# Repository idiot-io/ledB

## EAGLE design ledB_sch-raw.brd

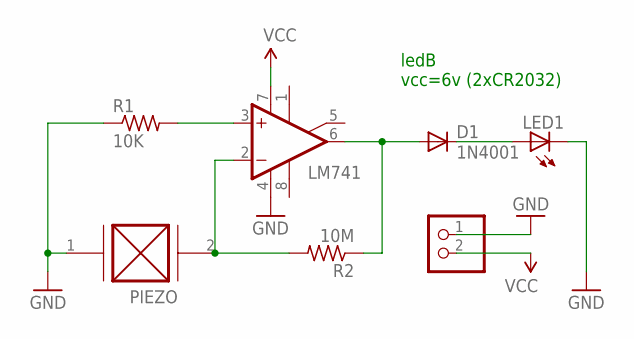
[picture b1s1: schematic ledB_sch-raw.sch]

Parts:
D1: 1N4001; DO-214AC
JP1: 6V+; 1X02_ROUND
LED1: LED1206; LED-1206
OPAMP: LM741; SO08
PIEZO: PIEZO; 1X02_ROUND
R1: 10K; M1206
R2: 10M; M1206

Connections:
GND: JP1.1, LED1.C, OPAMP.4 (V-), PIEZO.1 (GND), R1.1
unnamed: OPAMP.3 (+IN), R1.2
unnamed: D1.A, OPAMP.6 (OUT), R2.1
unnamed: D1.C, LED1.A
SIG: OPAMP.2 (-IN), PIEZO.2 (OUT+), R2.2
VCC: JP1.2, OPAMP.7 (V+)

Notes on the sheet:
ledB vcc=6v (2xCR2032)

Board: 2 copper layers, 7 parts (0 on the bottom side), 6 nets, no tracks yet.

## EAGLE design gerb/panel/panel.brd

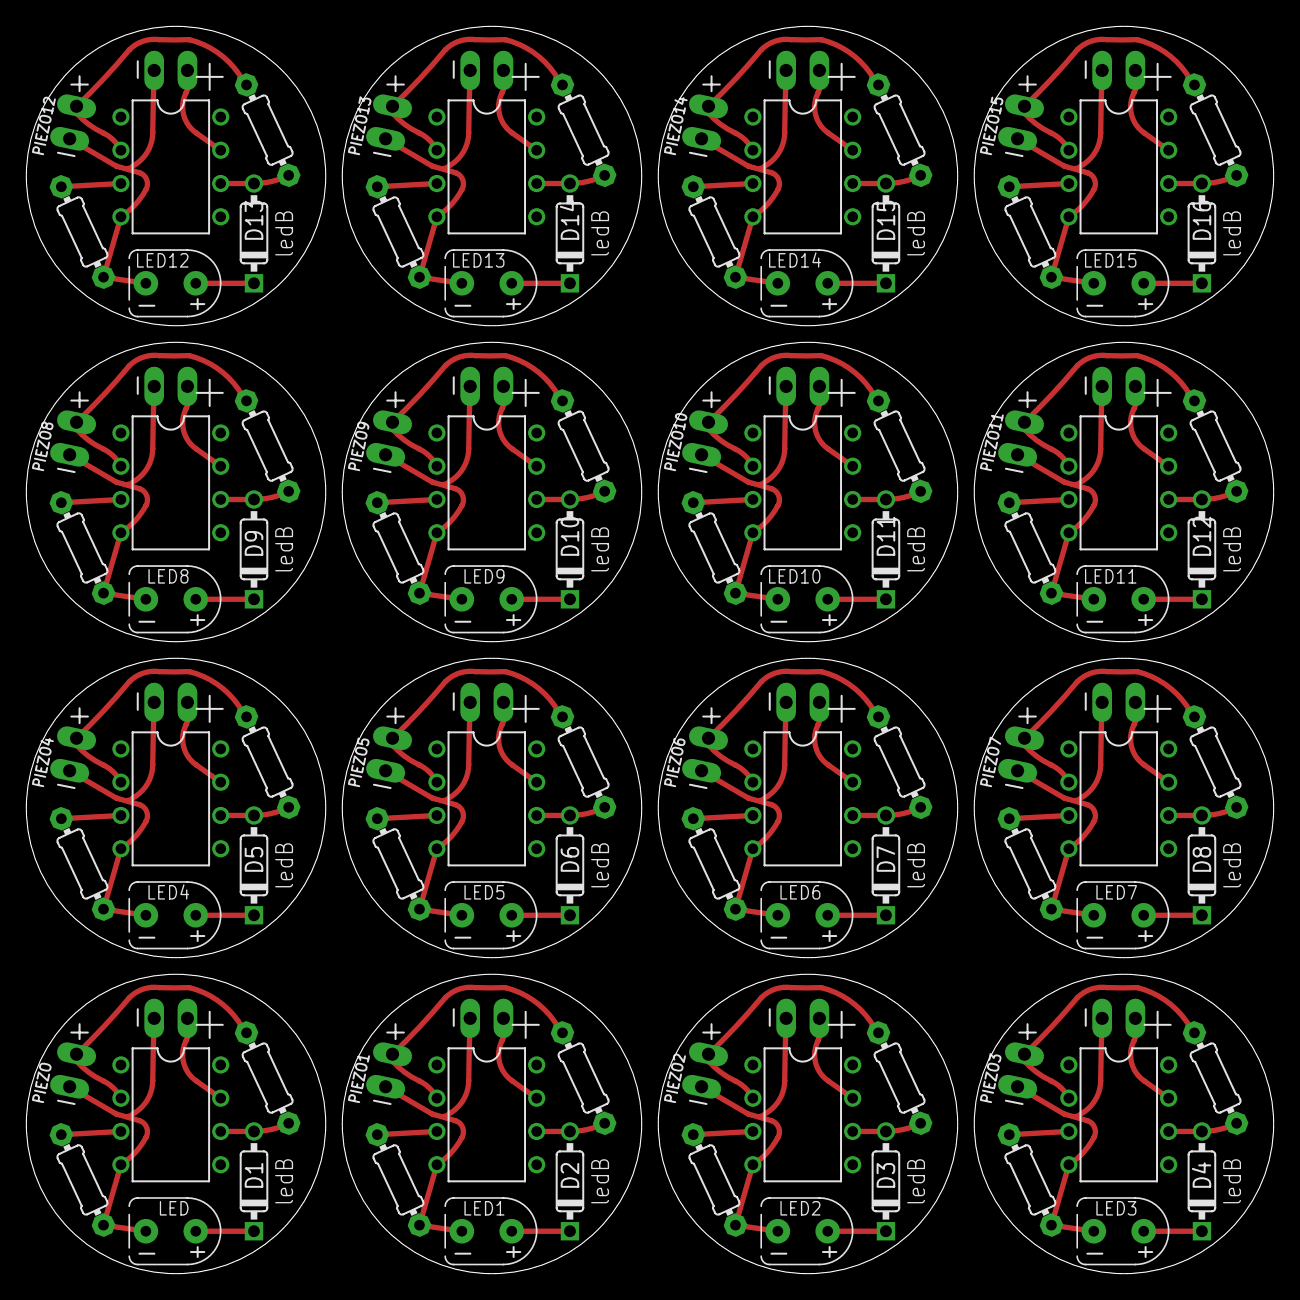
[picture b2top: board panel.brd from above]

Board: 2 copper layers, 95.2 x 95.2 mm, 112 parts (0 on the bottom side), 96 nets.

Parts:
D1, D2, D3, D4, D5, D6, D7, D8, D9, D10, D11, D12, D13, D14, D15, D16: diode; DO35-3
JP1, JP2, JP3, JP4, JP5, JP6, JP7, JP8, JP9, JP10, JP11, JP12, JP13, JP14, JP15, JP16: 6V+; 1X02_OVAL
LED, LED1, LED2, LED3, LED4, LED5, LED6, LED7, LED8, LED9, LED10, LED11, LED12, LED13, LED14, LED15: LED5MM
OPAMP, OPAMP1, OPAMP2, OPAMP3, OPAMP4, OPAMP5, OPAMP6, OPAMP7, OPAMP8, OPAMP9, OPAMP10, OPAMP11, OPAMP12, OPAMP13, OPAMP14, OPAMP15: LM741; DIL08
PIEZO, PIEZO1, PIEZO2, PIEZO3, PIEZO4, PIEZO5, PIEZO6, PIEZO7, PIEZO8, PIEZO9, PIEZO10, PIEZO11, PIEZO12, PIEZO13, PIEZO14, PIEZO15: PIEZO; 1X02_PEIZO
R1, R3, R5, R7, R9, R11, R13, R15, R17, R19, R21, R23, R25, R27, R29, R31: 10K; 0204/7
R2, R4, R6, R8, R10, R12, R14, R16, R18, R20, R22, R24, R26, R28, R30, R32: 10M; 0204/7

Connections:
GND: JP1.1, LED.K, OPAMP.4, PIEZO.1, R1.1
GND1: JP2.1, LED1.K, OPAMP1.4, PIEZO1.1, R3.1
GND2: JP3.1, LED2.K, OPAMP2.4, PIEZO2.1, R5.1
GND3: JP4.1, LED3.K, OPAMP3.4, PIEZO3.1, R7.1
GND4: JP5.1, LED4.K, OPAMP4.4, PIEZO4.1, R9.1
GND5: JP6.1, LED5.K, OPAMP5.4, PIEZO5.1, R11.1
GND6: JP7.1, LED6.K, OPAMP6.4, PIEZO6.1, R13.1
GND7: JP8.1, LED7.K, OPAMP7.4, PIEZO7.1, R15.1
GND8: JP9.1, LED8.K, OPAMP8.4, PIEZO8.1, R17.1
GND9: JP10.1, LED9.K, OPAMP9.4, PIEZO9.1, R19.1
GND10: JP11.1, LED10.K, OPAMP10.4, PIEZO10.1, R21.1
GND11: JP12.1, LED11.K, OPAMP11.4, PIEZO11.1, R23.1
GND12: JP13.1, LED12.K, OPAMP12.4, PIEZO12.1, R25.1
GND13: JP14.1, LED13.K, OPAMP13.4, PIEZO13.1, R27.1
GND14: JP15.1, LED14.K, OPAMP14.4, PIEZO14.1, R29.1
GND15: JP16.1, LED15.K, OPAMP15.4, PIEZO15.1, R31.1
unnamed: OPAMP.3, R1.2
unnamed: D1.A, OPAMP.6, R2.1
unnamed: D2.A, OPAMP1.6, R4.1
unnamed: D2.C, LED1.A
unnamed: D1.C, LED.A
unnamed: OPAMP1.3, R3.2
unnamed: D3.A, OPAMP2.6, R6.1
unnamed: D3.C, LED2.A
unnamed: OPAMP2.3, R5.2
unnamed: D4.A, OPAMP3.6, R8.1
unnamed: D4.C, LED3.A
unnamed: OPAMP3.3, R7.2
unnamed: D5.A, OPAMP4.6, R10.1
unnamed: D5.C, LED4.A
unnamed: OPAMP4.3, R9.2
unnamed: D6.A, OPAMP5.6, R12.1
unnamed: D6.C, LED5.A
unnamed: OPAMP5.3, R11.2
unnamed: D7.A, OPAMP6.6, R14.1
unnamed: D7.C, LED6.A
unnamed: OPAMP6.3, R13.2
unnamed: D8.A, OPAMP7.6, R16.1
unnamed: D8.C, LED7.A
unnamed: OPAMP7.3, R15.2
unnamed: D9.A, OPAMP8.6, R18.1
unnamed: D9.C, LED8.A
unnamed: OPAMP8.3, R17.2
unnamed: D10.A, OPAMP9.6, R20.1
unnamed: D10.C, LED9.A
unnamed: OPAMP9.3, R19.2
unnamed: D11.A, OPAMP10.6, R22.1
unnamed: D11.C, LED10.A
unnamed: OPAMP10.3, R21.2
unnamed: D12.A, OPAMP11.6, R24.1
unnamed: D12.C, LED11.A
unnamed: OPAMP11.3, R23.2
unnamed: D13.A, OPAMP12.6, R26.1
unnamed: D13.C, LED12.A
unnamed: OPAMP12.3, R25.2
unnamed: D14.A, OPAMP13.6, R28.1
unnamed: D14.C, LED13.A
unnamed: OPAMP13.3, R27.2
unnamed: D15.A, OPAMP14.6, R30.1
unnamed: D15.C, LED14.A
unnamed: OPAMP14.3, R29.2
unnamed: D16.A, OPAMP15.6, R32.1
unnamed: D16.C, LED15.A
unnamed: OPAMP15.3, R31.2
SIG: OPAMP.2, PIEZO.2, R2.2
SIG1: OPAMP1.2, PIEZO1.2, R4.2
SIG2: OPAMP2.2, PIEZO2.2, R6.2
SIG3: OPAMP3.2, PIEZO3.2, R8.2
SIG4: OPAMP4.2, PIEZO4.2, R10.2
SIG5: OPAMP5.2, PIEZO5.2, R12.2
SIG6: OPAMP6.2, PIEZO6.2, R14.2
SIG7: OPAMP7.2, PIEZO7.2, R16.2
SIG8: OPAMP8.2, PIEZO8.2, R18.2
SIG9: OPAMP9.2, PIEZO9.2, R20.2
SIG10: OPAMP10.2, PIEZO10.2, R22.2
SIG11: OPAMP11.2, PIEZO11.2, R24.2
SIG12: OPAMP12.2, PIEZO12.2, R26.2
SIG13: OPAMP13.2, PIEZO13.2, R28.2
SIG14: OPAMP14.2, PIEZO14.2, R30.2
SIG15: OPAMP15.2, PIEZO15.2, R32.2
VCC: JP1.2, OPAMP.7
VCC1: JP2.2, OPAMP1.7
VCC2: JP3.2, OPAMP2.7
VCC3: JP4.2, OPAMP3.7
VCC4: JP5.2, OPAMP4.7
VCC5: JP6.2, OPAMP5.7
VCC6: JP7.2, OPAMP6.7
VCC7: JP8.2, OPAMP7.7
VCC8: JP9.2, OPAMP8.7
VCC9: JP10.2, OPAMP9.7
VCC10: JP11.2, OPAMP10.7
VCC11: JP12.2, OPAMP11.7
VCC12: JP13.2, OPAMP12.7
VCC13: JP14.2, OPAMP13.7
VCC14: JP15.2, OPAMP14.7
VCC15: JP16.2, OPAMP15.7

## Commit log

2015-01-03 :space_invader: Added .gitattributes & .gitignore files
2015-01-03 one layer design
    for cutting with plotter or home etching
2015-01-08 fix schema, one layer round design
    and fixed the schema
2015-12-01 fat traces 24)
2015-12-25 lib piezo
2015-12-26 add image and fix schema
2015-12-26 add image and fix schema 2
2015-12-26 added topoR assited routing
2015-12-26 remove gitattribute
2017-07-01 round
2017-07-01 gerber
2017-07-02 mor gerb
2019-05-31 import eagle to svg
2019-05-31 ripup, 1206
